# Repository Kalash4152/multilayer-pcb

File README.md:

🖥️ My First Multi-Layer IoT PCB

This project is my first 4-layer PCB design, created as a multi-purpose IoT sensing board. The idea was to combine multiple sensing capabilities and essential peripherals into a single compact board that could serve as a foundation for different IoT applications.

🔧 Features

ESP32 as the main controller (WiFi + Bluetooth support)

Integrated sensors:

Temperature sensor

Light sensor

Sound sensor

Onboard peripherals:

USB port for communication and power

SD card slot for storage

Built-in memory card interface for data logging

Multi-purpose design → enables IoT prototyping, monitoring, and data collection in one platform

⚡ PCB Design Process

The board was designed in KiCad, with a focus on building a manufacturable and reliable 4-layer PCB.

Layer Stackup:
I applied the concepts of core and pre-preg to design the stackup properly. This allowed me to dedicate separate planes for power and ground, while keeping signal traces isolated and routed cleanly.

Footprints:
I used SnapEDA extensively for verified footprints of external components. For parts not available, I created custom footprints, ensuring correct pad sizes, clearances, and pin alignments.

Routing & Planes:

Power lines were routed with wider traces for better current handling

Ground lines and planes were carefully managed to reduce noise and ensure a solid reference plane

Signal lines were routed with attention to length, separation, and their role in the circuit (high-speed, analog, digital, etc.)

Zones were filled (power/ground) depending on the layer and requirement to maintain proper distribution and minimize EMI

Verification:

Conducted a full ERC (Electrical Rule Check) to eliminate schematic-level errors

Performed DRC (Design Rule Check) and ensured zero errors

Verified every footprint and component placement for manufacturing accuracy

📐 Learning Outcomes

Practical experience in multi-layer PCB design and the importance of proper stackup planning

Gained knowledge about separating power, ground, and signal routing for noise-free operation

Understood the importance of zone fills and copper planes in stable power delivery

Learned to balance auto-routing and manual routing for cleaner signal paths

Developed confidence in using KiCad + SnapEDA workflow for professional PCB design

🚀 Conclusion

This board was my first step into multi-layer IoT hardware design, combining sensors, storage, and communication in one platform. The process gave me valuable insight into PCB stackups, routing strategies, and verification techniques, which will help me in designing more complex boards in the future

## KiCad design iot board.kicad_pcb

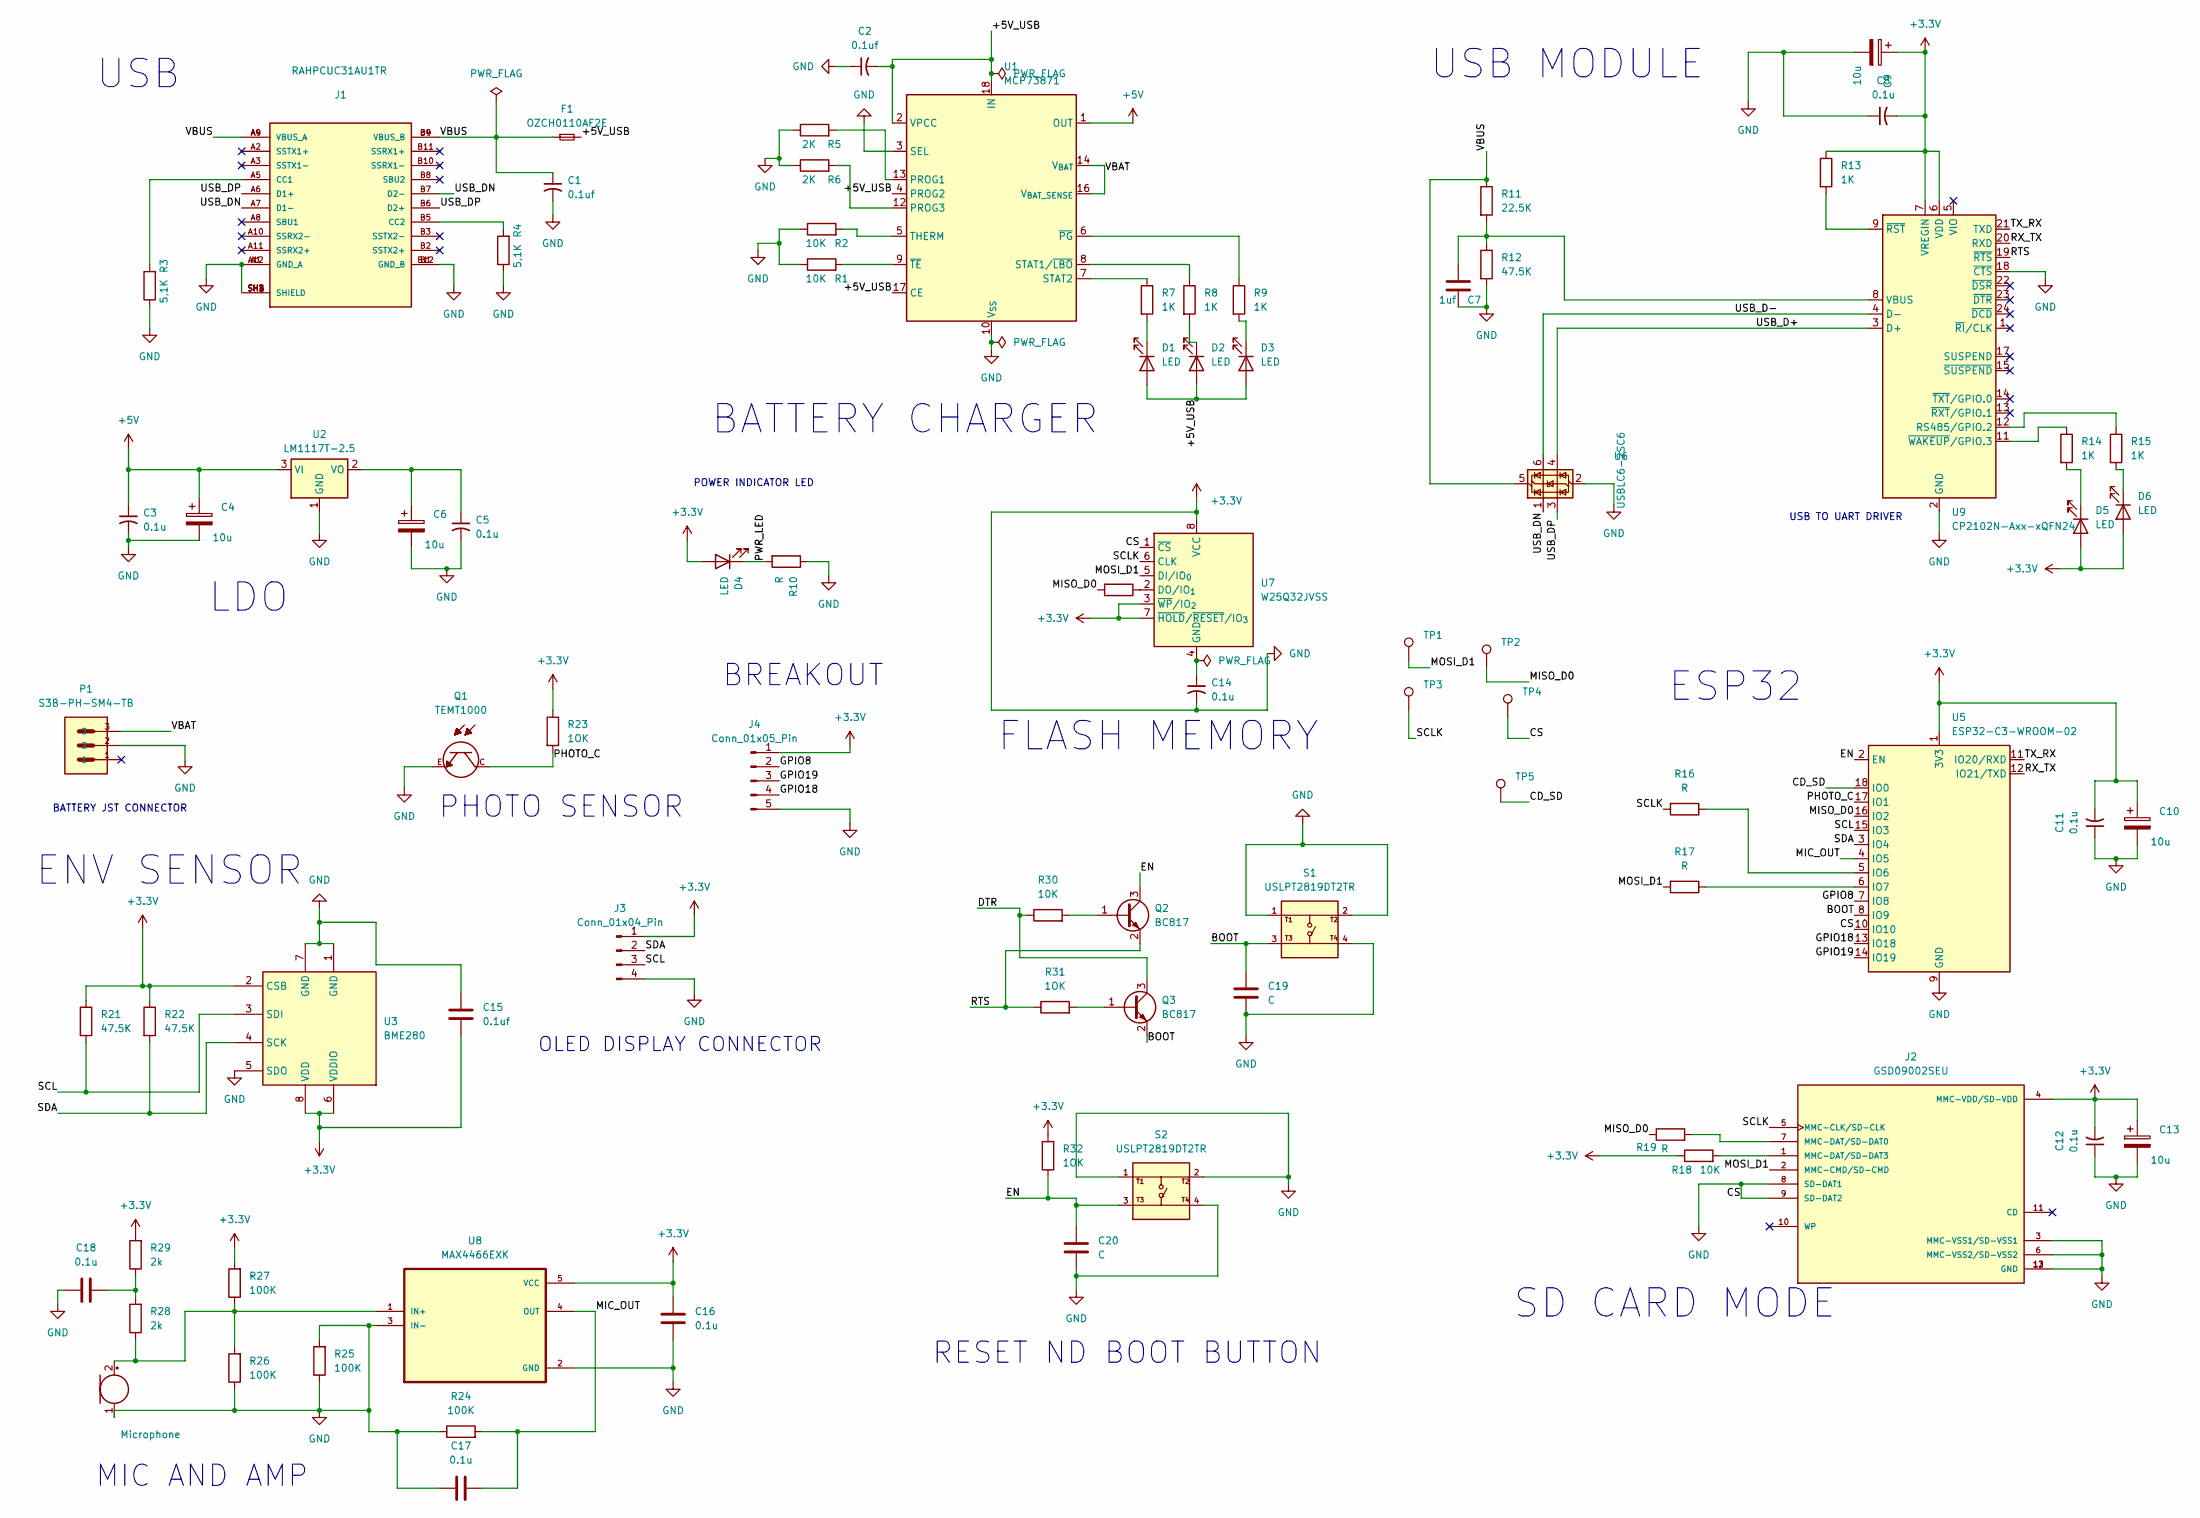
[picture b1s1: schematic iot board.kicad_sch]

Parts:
C1, C2, C15: 0.1uf; CP_Elec_4x5.4
C3, C5, C8, C11, C12, C14, C16, C17, C18: 0.1u; CP_Elec_4x5.4
C4, C6, C9, C10, C13: 10u; CP_Elec_4x5.4
C7: 1uf; CP_Elec_4x5.4
C19, C20: C; CP_Elec_4x5.4
D1, D2, D3, D4, D5, D6: LED; LED_0201_0603Metric_Pad0.64x0.40mm_HandSolder
F1: OZCH0110AF2E; Fuse_0402_1005Metric_Pad0.77x0.64mm_HandSolder
J1: RAHPCUC31AU1TR; SWITCHCRAFT_RAHPCUC31AU1TR; PARTREV A
J2: GSD09002SEU; AMPHENOL_GSD09002SEU; PARTREV D1
J3: Conn_01x04_Pin; PinHeader_1x04_P2.00mm_Vertical
J4: Conn_01x05_Pin; PinHeader_1x05_P2.00mm_Vertical
MK1: Microphone; MIC
P1: S3B-PH-SM4-TB; PinHeader_1x03_P1.27mm_Vertical
Q1: TEMT1000; XDCR_TEMT1000; DigiKey_Part_Number 751-1052-1-ND
Q2, Q3: BC817; SOT-23
R1, R2, R18, R30: 10K; R_0201_0603Metric_Pad0.64x0.40mm_HandSolder
R3, R4: 5,1K; R_0201_0603Metric_Pad0.64x0.40mm_HandSolder
R5, R6: 2K; R_0201_0603Metric_Pad0.64x0.40mm_HandSolder
R7, R8, R9, R13, R14, R15: 1K; R_0201_0603Metric_Pad0.64x0.40mm_HandSolder
R10, R16, R17, R19, R20: R; R_0201_0603Metric_Pad0.64x0.40mm_HandSolder
R11: 22.5K; R_0201_0603Metric_Pad0.64x0.40mm_HandSolder
R12, R21, R22: 47.5K; R_0201_0603Metric_Pad0.64x0.40mm_HandSolder
R23, R31, R32: 1OK; R_0201_0603Metric_Pad0.64x0.40mm_HandSolder
R24, R25, R26, R27: 100K; R_0201_0603Metric_Pad0.64x0.40mm_HandSolder
R28, R29: 2k; R_0201_0603Metric_Pad0.64x0.40mm_HandSolder
S1, S2: USLPT2819DT2TR; SW_USLPT2819DT2TR; PARTREV P
TP1: MOSI_D1; TestPoint_2Pads_Pitch2.54mm_Drill0.8mm
TP2: MISO_D0; TestPoint_2Pads_Pitch2.54mm_Drill0.8mm
TP3: SCLK; TestPoint_2Pads_Pitch2.54mm_Drill0.8mm
TP4, TP5: CS; TestPoint_2Pads_Pitch2.54mm_Drill0.8mm
U1: MCP73871; QFN-20-1EP_4x4mm_P0.5mm_EP2.5x2.5mm
U2: LM1117T-2.5; TO-220-3_Horizontal_TabDown
U3: BME280; Bosch_LGA-8_2.5x2.5mm_P0.65mm_ClockwisePinNumbering
U5: ESP32-C3-WROOM-02
U6: USBLC6-2SC6; SOT-23-6
U7: W25Q32JVSS; SOIC-8_5.3x5.3mm_P1.27mm
U8: MAX4466EXK; SOT65P210X110-5N; DigiKey_Part_Number MAX4466EXK+CT-ND
U9: CP2102N-Axx-xQFN24; QFN-24-1EP_4x4mm_P0.5mm_EP2.6x2.6mm

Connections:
+3.3V: C1.2, C2.1, C3.2, C4.2, C5.2, C6.2, C7.2, C8.1, C8.2, C9.1, C9.2, C10.1, C10.2, C11.1, C11.2, C12.1, C12.2, C13.1, C13.2, C14.2, C15.1, C15.2, C16.1, C16.2, C17.1, C18.1, C19.2, C20.2, D4.2 (A), D5.2 (A), D6.2 (A), J1.A1 (GND_A), J1.A12 (GND_A), J1.B1 (GND_B), J1.B12 (GND_B), J1.SH1 (SHIELD), J1.SH2 (SHIELD), J1.SH3 (SHIELD), J1.SH4 (SHIELD), J2.3 (MMC-VSS1/SD-VSS1), J2.4 (MMC-VDD/SD-VDD), J2.6 (MMC-VSS2/SD-VSS2), J2.8 (SD-DAT1), J2.9 (SD-DAT2), J2.12 (GND), J2.13 (GND), J3.1, J3.4, J4.1, J4.5, MK1.1 (-), P1.2, Q1.E, R1.1, R2.1, R3.1, R4.1, R5.1, R6.1, R10.1, R12.2, R13.1, R18.1, R21.1, R22.1, R23.1, R24.1, R25.1, R25.2, R26.1, R27.2, R29.2, R32.2, S1.1, S1.2, S1.4, S2.1, S2.2, S2.4, TP4.1, U1.3 (SEL), U1.10 (V_{SS}), U1.11 (V_{SS}), U1.21 (V_{SS}), U2.1 (GND), U3.1 (GND), U3.2 (CSB), U3.5 (SDO), U3.6 (VDDIO), U3.7 (GND), U3.8 (VDD), U5.1 (3V3), U5.9 (GND), U5.10 (IO10), U5.19 (GND), U6.2 (GND), U7.1 (~CS), U7.3 (~WP/IO_{2}), U7.7 (~HOLD/~RESET/IO_{3}), U7.8 (VCC), U8.2 (GND), U8.3 (IN-), U8.5 (VCC), U9.2 (GND), U9.6 (VDD), U9.7 (VREGIN), U9.18 (~CTS), U9.25 (GND)
+5V: C3.1, C4.1, U1.1 (OUT), U1.20 (OUT), U2.3 (VI)
/+5V_USB: C2.2, D1.2 (A), D2.2 (A), D3.2 (A), F1.2, U1.2 (VPCC), U1.4 (PROG2), U1.17 (CE), U1.18 (IN), U1.19 (IN)
/BOOT: C19.1, Q3.2 (E), S1.3, U5.8 (IO9)
/CD_SD: TP5.1, U5.18 (IO0)
/DTR: Q3.3 (C), R30.1
/EN: C20.1, Q2.3 (C), R32.1, S2.3, U5.2 (EN)
/GPIO8: J4.2, U5.7 (IO8)
/GPIO18: J4.4, U5.13 (IO18)
/GPIO19: J4.3, U5.14 (IO19)
/MIC_OUT: C17.2, R24.2, U5.4 (IO5), U8.4 (OUT)
/MISO_D0: R19.1, R20.2, TP2.1, U5.16 (IO2)
/MOSI_D1: J2.2 (MMC-CMD/SD-CMD), R17.2, TP1.1, U7.5 (DI/IO_{0})
/PHOTO_C: Q1.C, R23.2, U5.17 (IO1)
/PWR_LED: D4.1 (K), R10.2
/RTS: Q2.2 (E), R31.1, U9.19 (~RTS)
/RX_TX: U5.12 (IO21/TXD), U9.20 (RXD)
/SCL: J3.3, R21.2, U3.3 (SDI), U5.15 (IO3)
/SCLK: J2.5 (MMC-CLK/SD-CLK), R16.2, TP3.1, U7.6 (CLK)
/SDA: J3.2, R22.2, U3.4 (SCK), U5.3 (IO4)
/TX_RX: U5.11 (IO20/RXD), U9.21 (TXD)
/USB_D+: U6.4 (I/O2), U9.3 (D+)
/USB_D-: U6.6 (I/O1), U9.4 (D-)
/USB_DN: J1.A7 (D1-), J1.B7 (D2-), U6.1 (I/O1)
/USB_DP: J1.A6 (D1+), J1.B6 (D2+), U6.3 (I/O2)
/VBAT: P1.3, U1.14 (V_{BAT}), U1.15 (V_{BAT}), U1.16 (V_{BAT_SENSE})
/VBUS: C1.1, F1.1, J1.A4 (VBUS_A), J1.A9 (VBUS_A), J1.B4 (VBUS_B), J1.B9 (VBUS_B), R11.1, U6.5 (VBUS)
unnamed: C18.2, R28.2, R29.1
unnamed: D1.1 (K), R7.2
unnamed: D2.1 (K), R8.2
unnamed: D3.1 (K), R9.2
unnamed: D5.1 (K), R14.2
unnamed: D6.1 (K), R15.2
unnamed: J1.A5 (CC1), R3.2
unnamed: J1.B5 (CC2), R4.2
unnamed: J2.7 (MMC-DAT/SD-DAT0), R19.2
unnamed: J2.1 (MMC-DAT/SD-DAT3), R18.2
unnamed: MK1.2 (+), R26.2, R27.1, R28.1, U8.1 (IN+)
unnamed: Q2.1 (B), R30.2
unnamed: Q3.1 (B), R31.2
unnamed: R5.2, U1.13 (PROG1)
unnamed: R6.2, U1.12 (PROG3)
unnamed: R8.1, U1.8 (STAT1/~LBO)
unnamed: R7.1, U1.7 (STAT2)
unnamed: R2.2, U1.5 (THERM)
unnamed: R9.1, U1.6 (~PG)
unnamed: R1.2, U1.9 (~TE)
unnamed: C5.1, C6.1, U2.2 (VO)
unnamed: R16.1, U5.5 (IO6)
unnamed: R17.1, U5.6 (IO7)
unnamed: R20.1, U7.2 (DO/IO_{1})
unnamed: C14.1, U7.4 (GND)
unnamed: R15.1, U9.12 (RS485/GPIO.2)
unnamed: C7.1, R11.2, R12.1, U9.8 (VBUS)
unnamed: R13.2, U9.9 (~RST)
unnamed: R14.1, U9.11 (~WAKEUP/GPIO.3)

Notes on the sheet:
BATTERY CHARGER
LDO
ENV SENSOR
RESET ND BOOT BUTTON
POWER INDICATOR LED
BATTERY JST CONNECTOR
PHOTO SENSOR
FLASH MEMORY
ESP32
USB TO UART DRIVER
USB
MIC AND AMP
BREAKOUT
OLED DISPLAY CONNECTOR
SD CARD MODE
USB MODULE

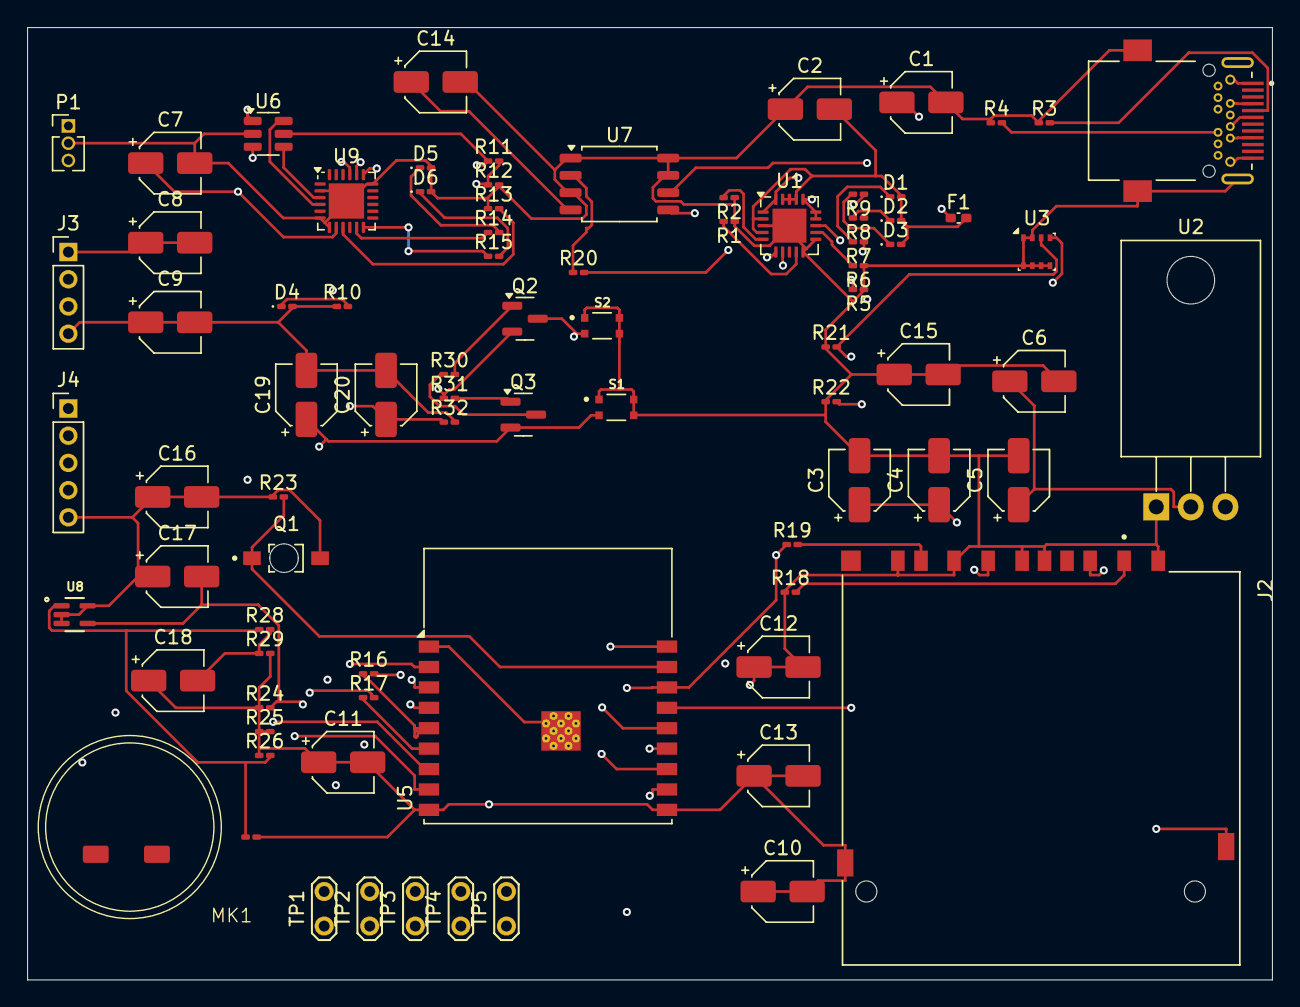
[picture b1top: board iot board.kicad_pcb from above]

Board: 4 copper layers, 91.5 x 70.0 mm, 83 parts (0 on the bottom side), 56 nets.
